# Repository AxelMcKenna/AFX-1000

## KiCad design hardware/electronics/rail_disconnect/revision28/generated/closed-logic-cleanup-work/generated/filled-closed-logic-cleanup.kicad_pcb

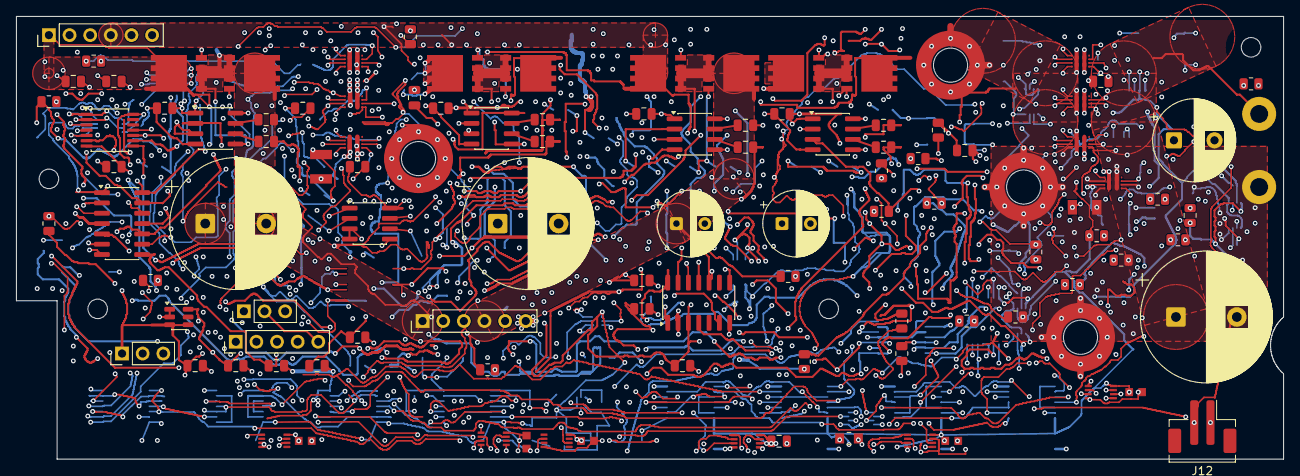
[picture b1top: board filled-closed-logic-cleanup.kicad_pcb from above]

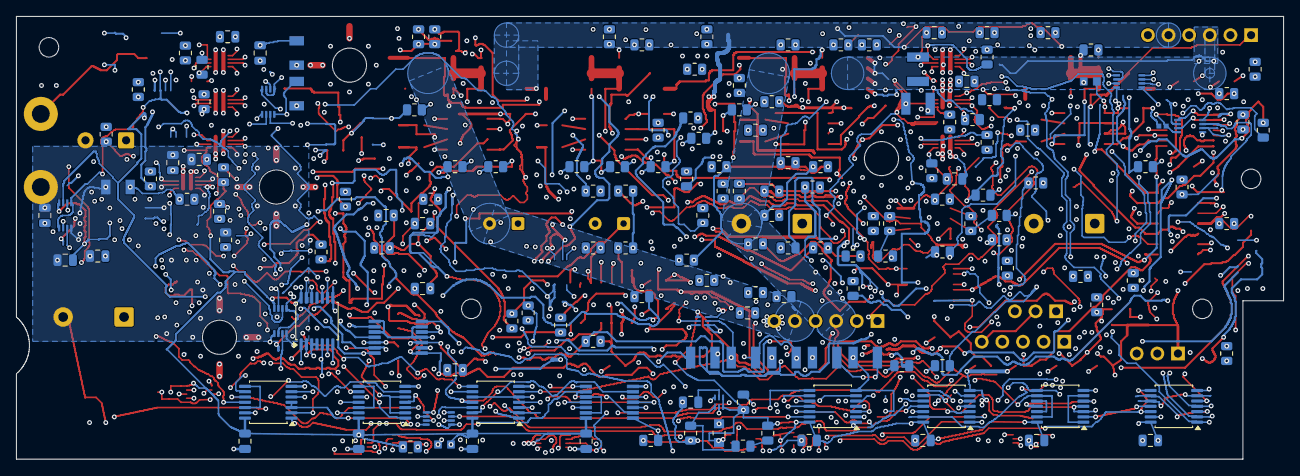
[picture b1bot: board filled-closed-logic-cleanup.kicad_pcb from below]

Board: 6 copper layers, 156.0 x 54.5 mm, 273 parts (160 on the bottom side), 198 nets.

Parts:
C1, C5, C9, C13, C17, C21, C25, C29, C34, C35, C36, C37, C57, C58, C59, C66, C67, C68, C69, C70, C71, C72, C73, C74, C75, C76, C77: 100nF 16V X7R; C_0805_2012Metric
C2, C3, C6, C7, C10, C11, C14, C15: 10pF 100V C0G 5%; C_0805_2012Metric
C4, C8: 1500uF 35V electrolytic 20% EEUFR1V152S; CP_Radial_D16.0mm_P7.50mm
C12, C16: 220uF 35V electrolytic 20% EEUFR1V221; CP_Radial_D8.0mm_P3.50mm
C20: 1500uF 16V electrolytic 20% EEUFR1C152; CP_Radial_D10.0mm_P5.00mm
C24: 4700uF 16V electrolytic 20% EEUFR1C472; CP_Radial_D16.0mm_P7.50mm
C26: 1uF 16V X7R; C_0805_2012Metric
C27, C28, C30, C31, C32, C33, C53, C54, C55, C56: 100pF 50V C0G 5%; C_0805_2012Metric
C38: 10uF 16V X7R; C_0805_2012Metric
C39, C41, C49, C61, C62, C63, C64, C65: 100nF 50V C0G 5% C1210C104J5GACTU; KEMET_C1210_LevelB
C40, C42, C44, C46, C48, C50, C52: 1uF 50V X7R; C_0805_2012Metric
C43, C45, C47, C51: 47nF 50V C0G 5% C1206C473J5GACTU; KEMET_C1206_LevelB
C60: 10nF 50V C0G 5%; C_0805_2012Metric
C78, C80, C81, C82, C83, C84, C85: 100nF 16V X7R 10% KEMET C0603C104K4RACTU; KEMET_C0603_LevelB
C79: 100nF 16V X7R 10% KEMET C0402C104K4RACTU; KEMET_C0402_LevelB
H1, H2, H3, H4: M2_CLEARANCE; M2_Clearance
J1, J3: Header6; PinHeader_1x06_P2.54mm_Vertical
J4: Alpha3079_AWG14_DIG_FORCE; AWG14_Force_2x1_P9mm_Engineering
J5, J6: Header3; PinHeader_1x03_P2.54mm_Vertical
J7, J8, J10, J11: 7466003R; 7466003R_M3_SMT_Annulus_NPTH
J9: E28 CONTROL; PinHeader_1x05_P2.54mm_Vertical
J12: JST B2B-PH-SM4-TB(LF)(SN); JST_B2B_PH_SM4_TB_MechanicalLands
Q1, Q2, Q3, Q4, Q5, Q6, Q7, Q8: CSD18540Q5B; CSD18540Q5B_TI_Q5B
R1, R9, R17, R25: 22 1%; R_0805_2012Metric
R2, R10, R18, R26, R60, R63, R68, R71, R76, R81, R86, R91: 20M 1%; R_0805_2012Metric
R3, R5, R11, R13, R19, R21, R27, R29, R61, R64, R69, R72, R77, R82, R87, R92, R93: 10k 1%; R_0805_2012Metric
R4, R12, R20, R28, R98, R102, R106, R110, R114, R118, R122: 100 1%; R_0805_2012Metric
R6, R7, R14, R15, R22, R23, R30, R31: 15k 1%; R_0805_2012Metric
R8, R16, R24, R32, R40, R48: 47k 1%; R_0805_2012Metric
R49: 150k 0.01% 5ppm; R_0805_2012Metric
R50: 6.2k 0.01% 5ppm; R_0805_2012Metric
R51, R54, R58, R59, R62, R66, R67, R70, R74, R75, R79, R80, R84, R85, R89, R90, R94, R124, R127, R130, R133: 10k 0.01% 5ppm; R_0805_2012Metric
R52, R55: 1k 1%; R_0805_2012Metric
R53: 100k 0.01% 5ppm; R_0805_2012Metric
R56: 143k 0.01% 5ppm; R_0805_2012Metric
R57: 3.3k 0.01% 5ppm; R_0805_2012Metric
R65: 90.9k 0.01% 5ppm; R_0805_2012Metric
R73, R78: 31.6k 0.01% 5ppm; R_0805_2012Metric
R83: 12.4k 0.01% 5ppm; R_0805_2012Metric
R88: 7.5k 0.01% 5ppm; R_0805_2012Metric
R95, R99, R103, R107, R111, R115, R119, R125, R128, R131, R134, R136, R141: 10k; R_0805_2012Metric
R96, R100, R104, R108, R112, R116, R120, R140: 47k; R_0805_2012Metric
R97, R101, R117: 2.43k 0.1%; R_0805_2012Metric
R105, R109, R113, R121: 604 0.1%; R_0805_2012Metric
R123, R126, R129, R132: 28.7k 0.01% 5ppm; R_0805_2012Metric
R135: 10k 0.1% 25ppm Panasonic ERA6AEB103V; Resistor_SMD_Panasonic_ERA6A_2012
R137: 11.1k 0.1%; R_0805_2012Metric
R138: 39.2 0.1%; R_0805_2012Metric
R139: 10k 0.1%; R_0805_2012Metric
R142: 15k; R_0805_2012Metric
R143: 15k 0.1% 25ppm Panasonic ERA6AEB153V; Resistor_SMD_Panasonic_ERA6A_2012
U1, U2, U3, U4: SI8751AB-ISR; SOIC-8_3.9x4.9mm_P1.27mm
U7: REF35125QDBVR; SOT-23-6
U8: OPA2333AID; SOIC-8_3.9x4.9mm_P1.27mm
U9, U10: TLV1824DR; SOIC-14_3.9x8.7mm_P1.27mm
U11, U12, U24, U25, U26, U27: SN74LVC08APWR; TSSOP-14_4.4x5mm_P0.65mm
U13, U14, U15, U16, U17, U32, U33: TPS259482LYWP; TPS259482L_YWP0012A
U18: TLV1824PWR; TLV1824_PW0014A
U19, U20: TPS389001DSET; TPS389001_DSE0006A
U21, U22: SN74LVC02APWR; TSSOP-14_4.4x5mm_P0.65mm
U23: SN74LVC32APWR; TSSOP-14_4.4x5mm_P0.65mm
U28: SN74LVC14APWR; SN74LVC14A_PW0014A
U29, U30, U31, U34: SN74AUP2G08DCUR; SN74AUP2G08_DCU0008A
U35, U36, U37, U38, U39, U40, U41, U42: SN74LVC3G17DCUR; SN74LVC3G17_DCU0008A

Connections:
/5V_DIG: C24.1, J4.1, R48.1, R132.1, U15.6, U15.11, U16.6, U16.11, U17.6, U17.11, U33.6, U33.11
/5V_DIG_OV_OK: R81.1, R82.2, U10.1, U37.6
/5V_DIG_OV_OK_SCHMITT: U11.10, U37.2
/5V_DIG_OV_REF: R80.2, R81.2, U10.7
/5V_DIG_OV_SENSE: C33.1, R78.2, R79.1, U10.6
/5V_DIG_SRC: C44.1, C46.1, C48.1, C52.1, J11.1, R78.1, R126.1, U15.5, U15.12, U16.5, U16.12, U17.5, U17.12, U33.5, U33.12
/AGND: C1.2, C4.2, C5.2, C8.1, C9.2, C12.2, C13.2, C16.1, C17.2, C20.2, C21.2, C24.2, C25.2, C26.2, C27.2, C28.2, C29.2, C30.2, C31.2, C32.2, C33.2, C34.2, C35.2, C36.2, C37.2, C38.2, C39.2, C40.2, C41.2, C42.2, C43.2, C44.2, C45.2, C46.2, C47.2, C48.2, C49.2, C50.2, C51.2, C52.2, C53.2, C54.2, C55.2, C56.2, C57.2, C58.2, C59.2, C60.2, C61.2, C62.2, C63.2, C64.2, C65.2, C66.2, C67.2, C68.2, C69.2, C70.2, C71.2, C72.2, C73.2, C74.2, C75.2, C76.2, C77.2, C78.2, C79.2, C80.2, C81.2, C82.2, C83.2, C84.2, C85.2, J1.2, J3.2, J4.2, J5.2, J6.1, J7.1, J8.1, J9.1, J12.2, R3.2, R5.2, R8.2, R11.2, R13.2, R16.2, R19.2, R21.2, R24.2, R27.2, R29.2, R32.2, R40.2, R48.2, R58.2, R66.2, R74.2, R79.2, R84.2, R89.2, R93.2, R94.2, R96.2, R97.2, R100.2, R101.2, R104.2, R105.2, R108.2, R109.2, R112.2, R113.2, R116.2, R117.2, R120.2, R121.2, R124.2, R127.2, R130.2, R133.2, R139.2, R140.2, R141.2, R142.2, R143.2, U1.4, U2.4, U3.4, U4.4, U7.1, U7.2, U8.3, U8.4, U8.5, U9.12, U10.12, U11.7, U12.7, U13.2, U13.4, U13.8, U14.2, U14.4, U14.8, U15.2, U15.4, U15.8, U16.2, U16.4, U16.8, U17.2, U17.4, U17.8, U18.12, U19.2, U20.2, U21.7, U22.7, U22.9, U22.12, U23.7, U24.7, U25.7, U26.7, U27.7, U28.7, U29.4, U30.4, U31.4, U32.2, U32.4, U32.8, U33.2, U33.4, U33.8, U34.4, U35.4, U36.4, U37.4, U38.4, U39.4, U40.4, U41.4, U42.3, U42.4, U42.6
/ALL_RAILS_ALLOW: U12.11, U21.2, U29.1
/ANA_OUTPUT_OK: R131.2, U18.14, U39.3
/ANA_OUTPUT_OK_SCHMITT: U24.4, U39.5
/ANA_PG0: R95.1, U13.3, U41.3
/ANA_PG0_SCHMITT: U31.2, U41.5
/ANA_PG1: R99.1, U14.3, U41.6
/ANA_PG1_SCHMITT: U34.6, U41.2
/ANA_PG2: R115.1, U32.3, U42.1
/ANA_PG2_SCHMITT: U26.10, U42.7
/ANA_SOURCE_OK: R125.2, U18.2, U38.6
/ANA_SOURCE_OK_SCHMITT: U24.1, U38.2
/DIG_OUTPUT_OK: R134.2, U18.13, U39.6
/DIG_OUTPUT_OK_SCHMITT: U24.5, U39.2
/DIG_PG0: R103.1, U15.3, U40.1
/DIG_PG0_SCHMITT: U29.6, U40.7
/DIG_PG1: R107.1, U16.3, U40.3
/DIG_PG1_SCHMITT: U30.2, U40.5
/DIG_PG2: R111.1, U17.3, U40.6
/DIG_PG2_SCHMITT: U34.1, U40.2
/DIG_PG3: R119.1, U33.3, U41.1
/DIG_PG3_SCHMITT: U26.9, U30.6, U41.7
/DIG_SOURCE_OK: R128.2, U18.1, U39.1
/DIG_SOURCE_OK_SCHMITT: U24.2, U39.7
/E28_ALL_CHANNELS_READY: U26.8, U26.12
/E28_ANA_0_DVDT: R98.1, U13.7
/E28_ANA_0_DVDT_CAP: C39.1, R98.2
/E28_ANA_0_ILM: R97.1, U13.9
/E28_ANA_1_DVDT: R102.1, U14.7
/E28_ANA_1_DVDT_CAP: C41.1, R102.2
/E28_ANA_1_ILM: R101.1, U14.9
/E28_ANA_2_DVDT: R118.1, U32.7
/E28_ANA_2_DVDT_CAP: C49.1, R118.2
/E28_ANA_2_ILM: R117.1, U32.9
/E28_ANA_ENABLE: R96.1, U13.1, U30.3
/E28_ANA_FOLLOW: R100.1, U14.1, U31.7
/E28_ANA_FOLLOW2: R116.1, U32.1, U34.3
/E28_ANA_OUT_SENSE: C55.1, R129.2, R130.1, U18.9
/E28_ANA_SRC_SENSE: C53.1, R123.2, R124.1, U18.5
/E28_ARMED: U21.3, U21.4, U25.9
/E28_ARM_BAR: U21.1, U21.6
/E28_AUX_CT: C60.1, U19.5
/E28_AUX_DIV: R137.2, R138.1
/E28_AUX_RESET_N: U31.5, U35.5
/E28_AUX_RESET_RAW: R135.1, U19.6, U35.3
/E28_AUX_SENSE: R138.2, R139.1, U19.1
/E28_AUX_VALID: U24.13, U28.3, U29.2, U31.3
/E28_DIG_0_DVDT: R106.1, U15.7
/E28_DIG_0_DVDT_CAP: C43.1, R106.2
/E28_DIG_0_ILM: R105.1, U15.9
/E28_DIG_1_DVDT: R110.1, U16.7
/E28_DIG_1_DVDT_CAP: C45.1, R110.2
/E28_DIG_1_ILM: R109.1, U16.9
/E28_DIG_2_DVDT: R114.1, U17.7
/E28_DIG_2_DVDT_CAP: C47.1, R114.2
/E28_DIG_2_ILM: R113.1, U17.9
/E28_DIG_3_DVDT: R122.1, U33.7
/E28_DIG_3_DVDT_CAP: C51.1, R122.2
/E28_DIG_3_ILM: R121.1, U33.9
/E28_DIG_FOLLOW1: R108.1, U16.1, U29.3
/E28_DIG_FOLLOW2: R112.1, U17.1, U30.7
/E28_DIG_FOLLOW3: R120.1, U33.1, U34.7
/E28_DIG_OUT_SENSE: C56.1, R132.2, R133.1, U18.11
/E28_DIG_SRC_SENSE: C54.1, R126.2, R127.1, U18.7
/E28_FAULT: J9.4, U21.9, U21.13, U23.5, U28.5
/E28_FAULT_A: U23.8, U23.12
/E28_FAULT_ANY: U23.11, U25.10
/E28_FAULT_BAR: U21.10, U21.12
/E28_FAULT_SET: U21.8, U25.8
/E28_MASTER_ENABLE: J6.2, J9.5, R4.1, R12.1, R20.1, R28.1, R104.1, R141.1, U15.1, U20.1, U20.3, U25.13, U27.2, U29.5, U29.7, U30.1, U30.5, U31.1, U34.2, U34.5
/E28_NORMAL_OK: U22.8, U27.8
/E28_NORMAL_PRE: U24.8, U27.9
/E28_NOT_AUX: U23.2, U28.4
/E28_NOT_FAULT: U27.13, U28.6
/E28_NOT_NORMAL_OK: U22.10, U23.9
/E28_NOT_OUT_READY: U22.13, U26.2, U26.5
/E28_NOT_RUN: U23.1, U28.2, U28.9
/E28_NOT_SOURCE_READY: U28.10, U28.13
/E28_OUTPUT_PERMISSION: U26.11, U27.1
/E28_OUTPUT_READY: J9.3, U25.6
/E28_OUT_ARMED: U22.3, U22.4, U26.1
/E28_OUT_ARM_BAR: U22.1, U22.6
/E28_OUT_READY: U22.11, U24.6, U25.12, U26.13
/E28_OUT_UV_FAULT: U23.10, U26.3
/E28_OUT_VALID_ACTIVE: U22.2, U25.11
/E28_RESET: U21.5, U21.11, U23.3, U23.4
/E28_RESET_OUT: U22.5, U23.6
/E28_RUN_AND_SOURCE: U24.12, U27.6
/E28_RUN_LOGIC: U27.4, U28.8
/E28_SAFE_REQUEST: R140.1, U12.13, U27.11
/E28_SAFE_STAGE: U25.3, U27.12
/E28_SOURCE_READY: U24.3, U24.9, U25.2
/E28_SOURCE_READY_LOGIC: U27.5, U27.10, U28.12
/E28_TIMEOUT: U26.4, U35.7
/E28_TIMEOUT_CT: C61.1, C62.1, C63.1, C64.1, C65.1, U20.5
/E28_TIMEOUT_FAULT: U23.13, U26.6
/E28_TIMEOUT_RAW: R136.1, U20.6, U35.1
/E28_USER_AUX: U24.11, U25.1
/N12: C16.2, J3.5, Q8.3, R31.1, R32.1
/N12_ALLOW: R28.2, R29.1, U4.3
/N12_COMMON: Q7.1, Q8.1, R26.2, U4.5
/N12_DRIVE: R25.1, U4.8
/N12_GATE: Q7.2, Q8.2, R25.2, R26.1
/N12_INV: R54.1, R55.1, U8.7
/N12_MCAP1: C14.2, U4.7
/N12_MCAP1_LIMIT: C14.1, R30.2
/N12_MCAP2: C15.2, U4.6
/N12_MCAP2_LIMIT: C15.1, R31.2
/N12_OV_OK: R71.1, R72.2, U9.13, U37.1
/N12_OV_OK_SCHMITT: U11.4, U37.7
/N12_OV_REF: R70.2, R71.2, U9.11
/N12_OV_SENSE: C28.1, R55.2, U9.10
/N12_SRC: J1.5, Q7.3, R30.1, R53.1
/N12_SUM: R53.2, R54.2, U8.6
/N12_TT: R27.1, U4.2
/N19: C8.2, J3.3, Q4.3, R15.1, R16.1
/N19_ALLOW: R12.2, R13.1, U2.3
/N19_COMMON: Q3.1, Q4.1, R10.2, U2.5
/N19_DRIVE: R9.1, U2.8
/N19_GATE: Q3.2, Q4.2, R9.2, R10.1
/N19_INPUT_MID: R49.2, R50.1
/N19_INV: R51.1, R52.1, U8.1
/N19_MCAP1: C6.2, U2.7
/N19_MCAP1_LIMIT: C6.1, R14.2
/N19_MCAP2: C7.2, U2.6
/N19_MCAP2_LIMIT: C7.1, R15.2
/N19_OV_OK: R63.1, R64.2, U9.1, U36.3
/N19_OV_OK_SCHMITT: U11.1, U36.5
/N19_OV_REF: R62.2, R63.2, U9.7
/N19_OV_SENSE: C27.1, R52.2, U9.6
/N19_SRC: J1.3, Q3.3, R14.1, R49.1
/N19_SUM: R50.2, R51.2, U8.2
/N19_TT: R11.1, U2.2
/NF_OUTPUT_VALID_RAW: J12.1, R143.1, U35.6
/NF_VALID_LOGIC: U25.5, U35.2
/OK_5: U11.8, U12.4
/OK_12: U11.6, U12.2
/OK_19: U11.3, U12.1
/OK_ALL_OV: U12.8, U12.12, U24.10
/OK_ANALOG: U12.3, U12.9
/OK_AUXILIARY: U12.6, U12.10
/OK_REF: U11.11, U12.5
/P03_SOURCES_READY: J9.2, R142.1, U28.11
/P12: C12.1, J3.4, Q6.3, R23.1, R24.1
/P12_ALLOW: R20.2, R21.1, U3.3
/P12_COMMON: Q5.1, Q6.1, R18.2, U3.5
/P12_DRIVE: R17.1, U3.8
/P12_GATE: Q5.2, Q6.2, R17.2, R18.1
/P12_MCAP1: C10.2, U3.7
/P12_MCAP1_LIMIT: C10.1, R22.2
/P12_MCAP2: C11.2, U3.6
/P12_MCAP2_LIMIT: C11.1, R23.2
/P12_OV_OK: R68.1, R69.2, U9.14, U36.6
/P12_OV_OK_SCHMITT: U11.5, U36.2
/P12_OV_REF: R67.2, R68.2, U9.9
/P12_OV_SENSE: C31.1, R65.2, R66.1, U9.8
/P12_SRC: J1.4, Q5.3, R22.1, R65.1
/P12_TT: R19.1, U3.2
/P19: C4.1, J3.1, Q2.3, R7.1, R8.1
/P19_ALLOW: R4.2, R5.1, U1.3
/P19_COMMON: Q1.1, Q2.1, R2.2, U1.5
/P19_DRIVE: R1.1, U1.8
/P19_GATE: Q1.2, Q2.2, R1.2, R2.1
/P19_MCAP1: C2.2, U1.7
/P19_MCAP1_LIMIT: C2.1, R6.2
/P19_MCAP2: C3.2, U1.6
/P19_MCAP2_LIMIT: C3.1, R7.2
/P19_OV_OK: R60.1, R61.2, U9.2, U36.1
/P19_OV_OK_SCHMITT: U11.2, U36.7
/P19_OV_REF: R59.2, R60.2, U9.5
/P19_OV_SENSE: C30.1, R57.2, R58.1, U9.4
/P19_SENSE_MID: R56.2, R57.1
/P19_SRC: J1.1, Q1.3, R6.1, R56.1
/P19_TT: R3.1, U1.2
/POS_OUTPUT_READY: U25.4, U27.3
/POWER_RUN: J5.3, R93.1, U28.1
/PROTECT_REF: C26.1, J6.3, R59.1, R62.1, R67.1, R70.1, R75.1, R80.1, R85.1, R94.1, U7.6, U10.10, U18.4, U18.6, U18.8, U18.10
/REF_HIGH_AUX: R88.2, R89.1, R90.1
/REF_HIGH_OK: R91.1, R92.2, U10.13, U38.3
/REF_HIGH_OK_SCHMITT: U11.13, U38.5
/REF_HIGH_POSITIVE: R90.2, R91.2, U10.11
/REF_LOW_AUX: R83.2, R84.1, U10.8
/REF_LOW_OK: R86.1, R87.2, U10.14, U38.1
/REF_LOW_OK_SCHMITT: U11.12, U38.7
/REF_LOW_POSITIVE: R85.2, R86.2, U10.9
/V2V5_AUX: C1.1, C5.1, C9.1, C13.1, C17.1, C21.1, C25.1, C29.1, C34.1, C35.1, C36.1, C37.1, C38.1, C57.1, C58.1, C59.1, C66.1, C67.1, C68.1, C69.1, C70.1, C71.1, C72.1, C73.1, C74.1, C75.1, C76.1, C77.1, C78.1, C79.1, C80.1, C81.1, C82.1, C83.1, C84.1, C85.1, J5.1, R61.1, R64.1, R69.1, R72.1, R77.1, R82.1, R83.1, R87.1, R88.1, R92.1, R95.2, R99.2, R103.2, R107.2, R111.2, R115.2, R119.2, R125.1, R128.1, R131.1, R134.1, R135.2, R136.2, R137.1, U1.1, U2.1, U3.1, U4.1, U7.3, U7.4, U8.8, U9.3, U10.3, U11.14, U12.14, U18.3, U19.3, U19.4, U20.4, U21.14, U22.14, U23.14, U24.14, U25.14, U26.14, U27.14, U28.14, U29.8, U30.8, U31.6, U31.8, U34.8, U35.8, U36.8, U37.8, U38.8, U39.8, U40.8, U41.8, U42.8
/V5_REG: C20.1, J3.6, R40.1, R129.1, U13.6, U13.11, U14.6, U14.11, U32.6, U32.11
/V5_REG_OV_OK: R76.1, R77.2, U10.2, U37.3
/V5_REG_OV_OK_SCHMITT: U11.9, U37.5
/V5_REG_OV_REF: R75.2, R76.2, U10.5
/V5_REG_OV_SENSE: C32.1, R73.2, R74.1, U10.4
/V5_REG_SRC: C40.1, C42.1, C50.1, J1.6, J10.1, R73.1, R123.1, U13.5, U13.12, U14.5, U14.12, U32.5, U32.12

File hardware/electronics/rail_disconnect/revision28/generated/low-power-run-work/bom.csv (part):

Reference,Part_or_value,Footprint,Source,Note
Q1,CSD18540Q5B,RMX_E28:CSD18540Q5B_TI_Q5B,https://www.ti.com/lit/ds/symlink/csd18540q5b.pdf,KiCad grouped footprint pads:1=S physical1..3;2=G physical4;3=D physical5..8/exposed drain. Footprint candidate; dimension/stencil approval open.
Q2,CSD18540Q5B,RMX_E28:CSD18540Q5B_TI_Q5B,https://www.ti.com/lit/ds/symlink/csd18540q5b.pdf,KiCad grouped footprint pads:1=S physical1..3;2=G physical4;3=D physical5..8/exposed drain. Footprint candidate; dimension/stencil approval open.
U1,SI8751AB-ISR,Package_SO:SOIC-8_3.9x4.9mm_P1.27mm,https://www.skyworksinc.com/-/media/SkyWorks/SL/documents/pu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,Floating gate power is generated internally. No main-rail startup dependency.35us maximum turn-off uses100pF load and is NOT a bound for these MOSFETs.
R1,22 1%,Resistor_SMD:R_0805_2012Metric,,
R2,20M 1%,Resistor_SMD:R_0805_2012Metric,,Gate leakage budget includes both FETs; do not substitute a low-value gate-source shunt
R3,10k 1%,Resistor_SMD:R_0805_2012Metric,,
R4,100 1%,Resistor_SMD:R_0805_2012Metric,,
R5,10k 1%,Resistor_SMD:R_0805_2012Metric,,Receiving pulldown; missing interlock drive is OFF under10uA input-leakage allocation
C1,100nF 16V X7R,Capacitor_SMD:C_0805_2012Metric,,
R6,15k 1%,Resistor_SMD:R_0805_2012Metric,,Limits step-driven MCAP current; 60V across minimum14.85k is below6mA. Actual clamp sensitivity/dVdt qualification open.
C2,10pF 100V C0G 5%,Capacitor_SMD:C_0805_2012Metric,,Both drain transients monitored; no blanket surge/dVdt approval
R7,15k 1%,Resistor_SMD:R_0805_2012Metric,,Limits step-driven MCAP current; 60V across minimum14.85k is below6mA. Actual clamp sensitivity/dVdt qualification open.
C3,10pF 100V C0G 5%,Capacitor_SMD:C_0805_2012Metric,,Both drain transients monitored; no blanket surge/dVdt approval
C4,1500uF 35V electrolytic 20% EEUFR1V152S,Capacitor_THT:CP_Radial_D16.0mm_P7.50mm,https://industrial.panasonic.com/cdbs/www-data/pdf/RDF0000/A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,"Panasonic FR candidate; nominal D16x20/P7.5 for19V,D16x25/P7.5 digital,D8x11.5/P3.5 for12V,D10x20/P5 analog5V. ESR/ripple/aging,regulator stability,inrush and fit need qualification."
R8,47k 1%,Resistor_SMD:R_0805_2012Metric,,Protected-side bleed is not a rapid discharge or safety-isolation guarantee
Q3,CSD18540Q5B,RMX_E28:CSD18540Q5B_TI_Q5B,https://www.ti.com/lit/ds/symlink/csd18540q5b.pdf,KiCad grouped footprint pads:1=S physical1..3;2=G physical4;3=D physical5..8/exposed drain. Footprint candidate; dimension/stencil approval open.
Q4,CSD18540Q5B,RMX_E28:CSD18540Q5B_TI_Q5B,https://www.ti.com/lit/ds/symlink/csd18540q5b.pdf,KiCad grouped footprint pads:1=S physical1..3;2=G physical4;3=D physical5..8/exposed drain. Footprint candidate; dimension/stencil approval open.
U2,SI8751AB-ISR,Package_SO:SOIC-8_3.9x4.9mm_P1.27mm,https://www.skyworksinc.com/-/media/SkyWorks/SL/documents/pu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,Floating gate power is generated internally. No main-rail startup dependency.35us maximum turn-off uses100pF load and is NOT a bound for these MOSFETs.
R9,22 1%,Resistor_SMD:R_0805_2012Metric,,
R10,20M 1%,Resistor_SMD:R_0805_2012Metric,,Gate leakage budget includes both FETs; do not substitute a low-value gate-source shunt
R11,10k 1%,Resistor_SMD:R_0805_2012Metric,,
R12,100 1%,Resistor_SMD:R_0805_2012Metric,,
R13,10k 1%,Resistor_SMD:R_0805_2012Metric,,Receiving pulldown; missing interlock drive is OFF under10uA input-leakage allocation
C5,100nF 16V X7R,Capacitor_SMD:C_0805_2012Metric,,
R14,15k 1%,Resistor_SMD:R_0805_2012Metric,,Limits step-driven MCAP current; 60V across minimum14.85k is below6mA. Actual clamp sensitivity/dVdt qualification open.
C6,10pF 100V C0G 5%,Capacitor_SMD:C_0805_2012Metric,,Both drain transients monitored; no blanket surge/dVdt approval
R15,15k 1%,Resistor_SMD:R_0805_2012Metric,,Limits step-driven MCAP current; 60V across minimum14.85k is below6mA. Actual clamp sensitivity/dVdt qualification open.
C7,10pF 100V C0G 5%,Capacitor_SMD:C_0805_2012Metric,,Both drain transients monitored; no blanket surge/dVdt approval
C8,1500uF 35V electrolytic 20% EEUFR1V152S,Capacitor_THT:CP_Radial_D16.0mm_P7.50mm,https://industrial.panasonic.com/cdbs/www-data/pdf/RDF0000/A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,"Panasonic FR candidate; nominal D16x20/P7.5 for19V,D16x25/P7.5 digital,D8x11.5/P3.5 for12V,D10x20/P5 analog5V. ESR/ripple/aging,regulator stability,inrush and fit need qualification."
R16,47k 1%,Resistor_SMD:R_0805_2012Metric,,Protected-side bleed is not a rapid discharge or safety-isolation guarantee
Q5,CSD18540Q5B,RMX_E28:CSD18540Q5B_TI_Q5B,https://www.ti.com/lit/ds/symlink/csd18540q5b.pdf,KiCad grouped footprint pads:1=S physical1..3;2=G physical4;3=D physical5..8/exposed drain. Footprint candidate; dimension/stencil approval open.
Q6,CSD18540Q5B,RMX_E28:CSD18540Q5B_TI_Q5B,https://www.ti.com/lit/ds/symlink/csd18540q5b.pdf,KiCad grouped footprint pads:1=S physical1..3;2=G physical4;3=D physical5..8/exposed drain. Footprint candidate; dimension/stencil approval open.
U3,SI8751AB-ISR,Package_SO:SOIC-8_3.9x4.9mm_P1.27mm,https://www.skyworksinc.com/-/media/SkyWorks/SL/documents/pu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,Floating gate power is generated internally. No main-rail startup dependency.35us maximum turn-off uses100pF load and is NOT a bound for these MOSFETs.
R17,22 1%,Resistor_SMD:R_0805_2012Metric,,
R18,20M 1%,Resistor_SMD:R_0805_2012Metric,,Gate leakage budget includes both FETs; do not substitute a low-value gate-source shunt
R19,10k 1%,Resistor_SMD:R_0805_2012Metric,,
R20,100 1%,Resistor_SMD:R_0805_2012Metric,,
R21,10k 1%,Resistor_SMD:R_0805_2012Metric,,Receiving pulldown; missing interlock drive is OFF under10uA input-leakage allocation
C9,100nF 16V X7R,Capacitor_SMD:C_0805_2012Metric,,
R22,15k 1%,Resistor_SMD:R_0805_2012Metric,,Limits step-driven MCAP current; 60V across minimum14.85k is below6mA. Actual clamp sensitivity/dVdt qualification open.
C10,10pF 100V C0G 5%,Capacitor_SMD:C_0805_2012Metric,,Both drain transients monitored; no blanket surge/dVdt approval
R23,15k 1%,Resistor_SMD:R_0805_2012Metric,,Limits step-driven MCAP current; 60V across minimum14.85k is below6mA. Actual clamp sensitivity/dVdt qualification open.
C11,10pF 100V C0G 5%,Capacitor_SMD:C_0805_2012Metric,,Both drain transients monitored; no blanket surge/dVdt approval
C12,220uF 35V electrolytic 20% EEUFR1V221,Capacitor_THT:CP_Radial_D8.0mm_P3.50mm,https://industrial.panasonic.com/cdbs/www-data/pdf/RDF0000/A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,"Panasonic FR candidate; nominal D16x20/P7.5 for19V,D16x25/P7.5 digital,D8x11.5/P3.5 for12V,D10x20/P5 analog5V. ESR/ripple/aging,regulator stability,inrush and fit need qualification."
R24,47k 1%,Resistor_SMD:R_0805_2012Metric,,Protected-side bleed is not a rapid discharge or safety-isolation guarantee
Q7,CSD18540Q5B,RMX_E28:CSD18540Q5B_TI_Q5B,https://www.ti.com/lit/ds/symlink/csd18540q5b.pdf,KiCad grouped footprint pads:1=S physical1..3;2=G physical4;3=D physical5..8/exposed drain. Footprint candidate; dimension/stencil approval open.
Q8,CSD18540Q5B,RMX_E28:CSD18540Q5B_TI_Q5B,https://www.ti.com/lit/ds/symlink/csd18540q5b.pdf,KiCad grouped footprint pads:1=S physical1..3;2=G physical4;3=D physical5..8/exposed drain. Footprint candidate; dimension/stencil approval open.
U4,SI8751AB-ISR,Package_SO:SOIC-8_3.9x4.9mm_P1.27mm,https://www.skyworksinc.com/-/media/SkyWorks/SL/documents/pu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,Floating gate power is generated internally. No main-rail startup dependency.35us maximum turn-off uses100pF load and is NOT a bound for these MOSFETs.
R25,22 1%,Resistor_SMD:R_0805_2012Metric,,
R26,20M 1%,Resistor_SMD:R_0805_2012Metric,,Gate leakage budget includes both FETs; do not substitute a low-value gate-source shunt
R27,10k 1%,Resistor_SMD:R_0805_2012Metric,,
R28,100 1%,Resistor_SMD:R_0805_2012Metric,,
R29,10k 1%,Resistor_SMD:R_0805_2012Metric,,Receiving pulldown; missing interlock drive is OFF under10uA input-leakage allocation
C13,100nF 16V X7R,Capacitor_SMD:C_0805_2012Metric,,
R30,15k 1%,Resistor_SMD:R_0805_2012Metric,,Limits step-driven MCAP current; 60V across minimum14.85k is below6mA. Actual clamp sensitivity/dVdt qualification open.
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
